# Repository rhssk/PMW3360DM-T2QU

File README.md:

# PMW3360DM-T2QU
PCB schematic and design for the Pixart PMW3360DM-T2QU optical mouse sensor.

## Components
* 1 x [Pixart PMW3360DM-T2QU](https://www.pixart.com/products-detail/10/PMW3360DM-T2QU)
* 1 x [4.7uF/10V](http://uk.farnell.com/multicomp/mctt21f475z100ct/cap-mlcc-y5v-4-7uf-10v-0805-reel/dp/2666292)
* 1 x [1uF](http://uk.farnell.com/walsin/0805b105k100ct/cap-mlcc-x7r-1uf-10v-0805-reel/dp/2495444)
* 1 x [0.1uF](http://uk.farnell.com/walsin/0805b104k500ct/capacitor-mlcc-x7r-0-1uf-50v-0805/dp/2496944RL)
* 3 x [10K Ohm](http://uk.farnell.com/multicomp/mcwr08x1002ftl/res-thick-film-10k-1-0-125w-0805/dp/2447553)
* 1 x [130 Ohm](http://uk.farnell.com/multicomp/mcwr08x1300ftl/res-thick-film-130-ohm-1-0-125w/dp/2447568?ost=2447568)
* 1 x [39 Ohm](http://uk.farnell.com/multicomp/mcwr08x39r0ftl/res-thick-film-39r-1-0-125w-0805/dp/2447647?ost=2447647)
* 1 x [TLV70019DDCT 1.9V LDO](http://uk.farnell.com/texas-instruments/tlv70019ddct/ldo-reg-0-175vdo-0-2a-1-9v-5sot23/dp/2144265)
* 1 x [1x7 1.27mm pin header](https://uk.farnell.com/multicomp/mc-hvt1-s07-g/connector-header-7pos-1row-1-27mm/dp/2852589)

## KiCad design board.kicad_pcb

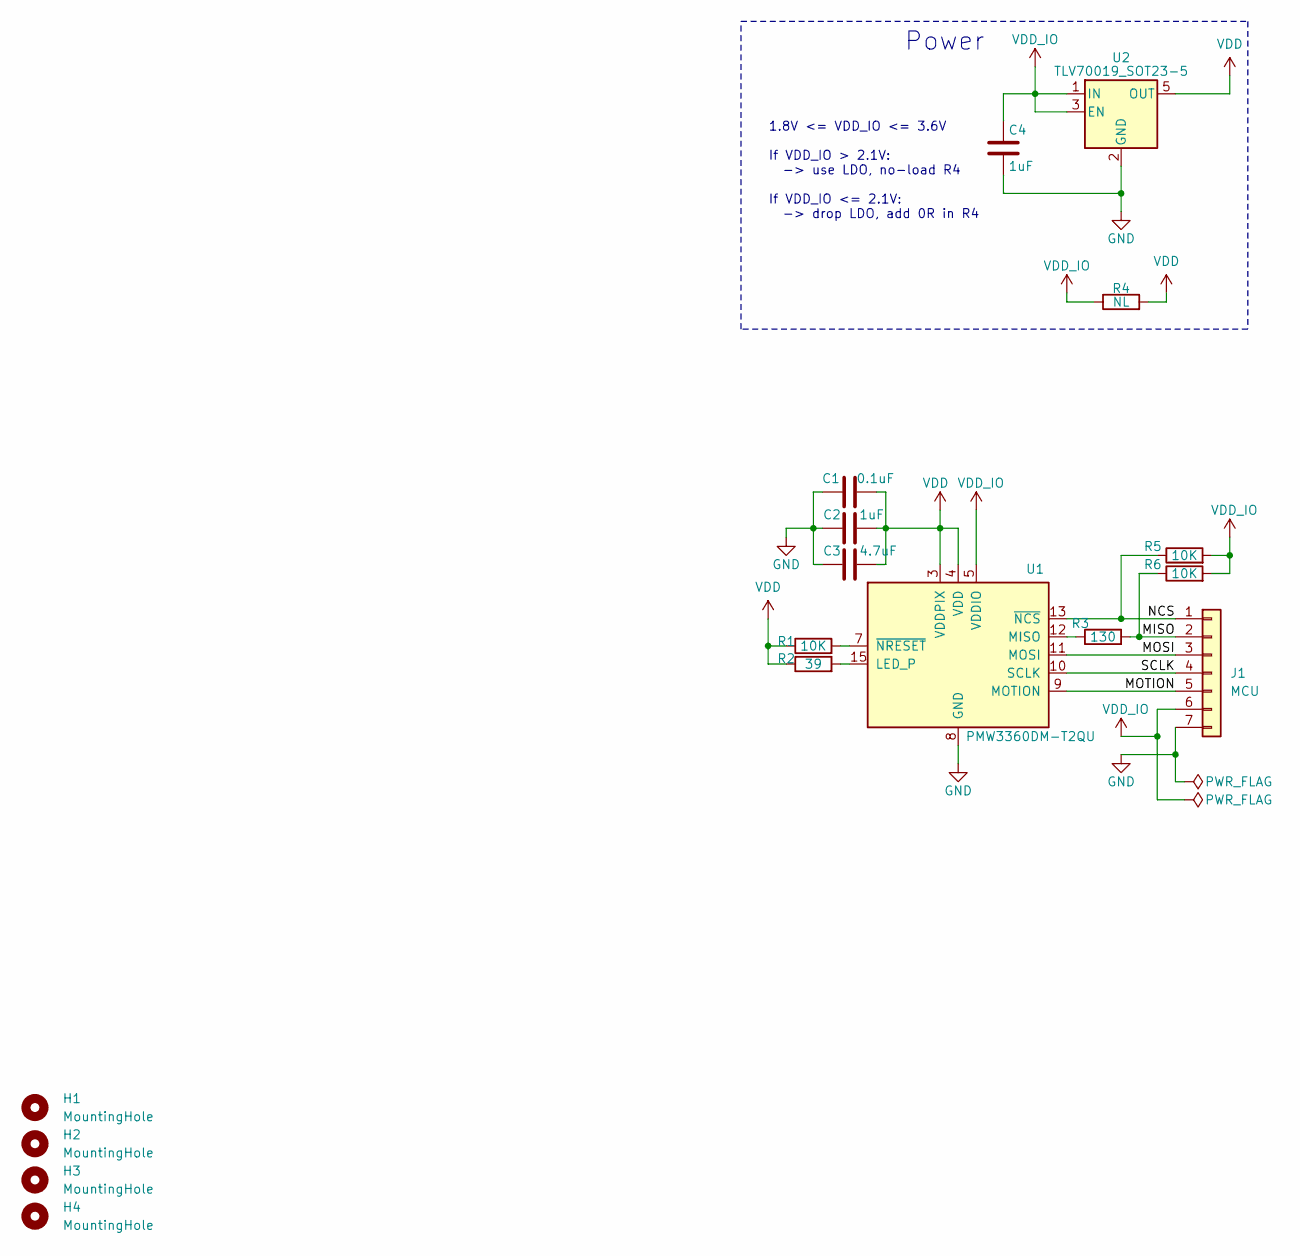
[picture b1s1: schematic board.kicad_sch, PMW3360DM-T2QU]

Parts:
C1: 0.1uF; C_0805_2012Metric
C2, C4: 1uF; C_0805_2012Metric
C3: 4.7uF; C_0805_2012Metric
H1, H2, H3, H4: MountingHole; MountingHole_2.2mm_M2_Pad_Via
J1: MCU; PinHeader_1x07_P1.27mm_Vertical
R1, R5, R6: 10K; R_0805_2012Metric
R2: 39; R_0805_2012Metric
R3: 130; R_0805_2012Metric
R4: NL; R_0805_2012Metric
U1: PMW3360DM-T2QU
U2: TLV70019_SOT23-5; SOT-23-5

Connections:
/MISO: J1.2, R3.2, R6.1
/MOSI: J1.3, U1.11 (MOSI)
/MOTION: J1.5, U1.9 (MOTION)
/NCS: J1.1, R5.1, U1.13 (~NCS~)
/SCLK: J1.4, U1.10 (SCLK)
GND: C1.1, C2.2, C3.2, C4.2, J1.7, U1.8 (GND), U2.2 (GND)
unnamed: R1.2, U1.7 (~NRESET~)
unnamed: R2.2, U1.15 (LED_P)
unnamed: R3.1, U1.12 (MISO)
VDD: C1.2, C2.1, C3.1, R1.1, R2.1, R4.2, U1.3 (VDDPIX), U1.4 (VDD), U2.5 (OUT)
VDD_IO: C4.1, J1.6, R4.1, R5.2, R6.2, U1.5 (VDDIO), U2.1 (IN), U2.3 (EN)
no_connect_12: U1.1 (NC)
no_connect_13: U1.2 (NC)
no_connect_14: U1.6 (NC)
no_connect_15: U1.14 (NC)
no_connect_16: U1.16 (NC)
no_connect_17: U2.4 (NC)

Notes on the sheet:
1.8V <= VDD_IO <= 3.6V If VDD_IO > 2.1V: -> use LDO, no-load R4 If VDD_IO <= 2.1V: -> drop LDO, add 0R in R4
Power

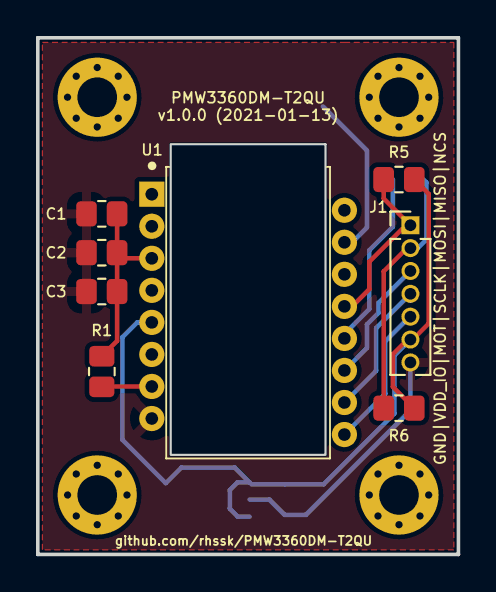
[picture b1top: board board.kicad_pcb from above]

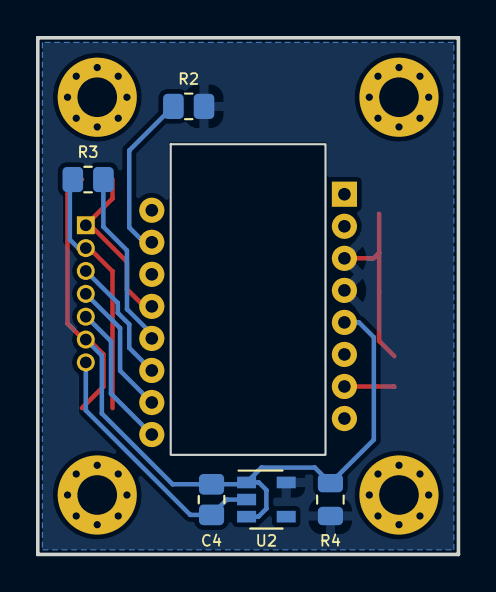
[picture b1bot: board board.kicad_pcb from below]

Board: 2 copper layers, 23.4 x 28.7 mm, 17 parts (5 on the bottom side), 11 nets.

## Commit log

2018-06-19 Mounting holes
2018-06-19 Add LICENSE
2018-06-19 Add PCB previews
2018-06-19 Add README
2018-06-19 Add manf#
2018-06-19 Fix component links
2018-06-19 README formatting
2018-07-03 Describe header pins on silkscreen
2018-07-03 Include fresh Gerbers
2018-07-03 Remove generated PDFs from Gerbers
2021-01-12 Release 1.0.0
